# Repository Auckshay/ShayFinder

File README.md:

# ShayFinder
A Multimedia Controller

(3D model)

## Why I made this project

I've always wanted a fast way to pause and play my media without compremising the function of any keys on my main keyboard. I saw the pathfinder template as a great place to build on my desire.

## Schematic

## PCB

## B.O.M.

|Name                                |Purpose                                          |Quantity|Total Cost (USD)|Link                                                                             |Distributor|
|------------------------------------|-------------------------------------------------|--------|----------------|---------------------------------------------------------------------------------|-----------|
|PCB                                 |For mounting and connecting all components       |5       |5.00            |http://pcbway.com/orderonline.aspx?outsideid=923c8937-0e41-439f-b9aa-470abffc90b2|PCBWAY     |
|220 ohm Reistors                    |so LEDs don't burn out                           |1       |0.99            |https://www.aliexpress.us/item/3256811700129159.html                             |AliExpress |
|LEDs                                |indicator for when switch is pressed (looks cool)|1       |2.32            |https://www.aliexpress.us/item/3256807854481666.html                             |AliExpress |
|Keyboard Switches (Cherry MX Design)|Human Interaction for controlling device         |1       |3.13            |https://www.aliexpress.us/item/3256806762410255.html                             |AliExpress |
|Seeedorino XIAO RP2040              |The brains for my entire project                 |1       |10.99           |https://a.co/d/0gEoytSN                                                          |Amazon     |

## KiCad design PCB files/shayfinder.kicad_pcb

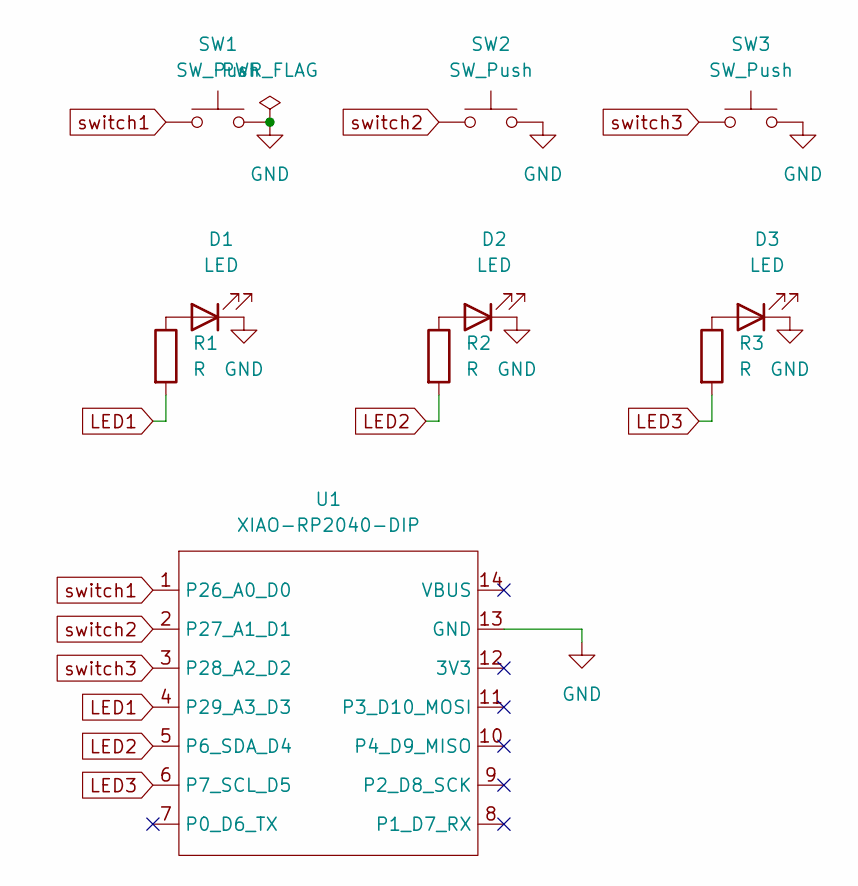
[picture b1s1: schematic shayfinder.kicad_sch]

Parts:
D1, D2, D3: LED; LED_D3.0mm_FlatTop
R1, R2, R3: R; R_Axial_DIN0204_L3.6mm_D1.6mm_P5.08mm_Horizontal
SW1, SW2, SW3: SW_Push; SW_Cherry_MX_1.00u_PCB
U1: XIAO-RP2040-DIP

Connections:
GND: D1.1 (K), D2.1 (K), D3.1 (K), SW1.2, SW2.2, SW3.2, U1.13 (GND)
LED1: R1.2, U1.4 (P29_A3_D3)
LED2: R2.2, U1.5 (P6_SDA_D4)
LED3: R3.2, U1.6 (P7_SCL_D5)
unnamed: D1.2 (A), R1.1
unnamed: D2.2 (A), R2.1
unnamed: D3.2 (A), R3.1
switch1: SW1.1, U1.1 (P26_A0_D0)
switch2: SW2.1, U1.2 (P27_A1_D1)
switch3: SW3.1, U1.3 (P28_A2_D2)

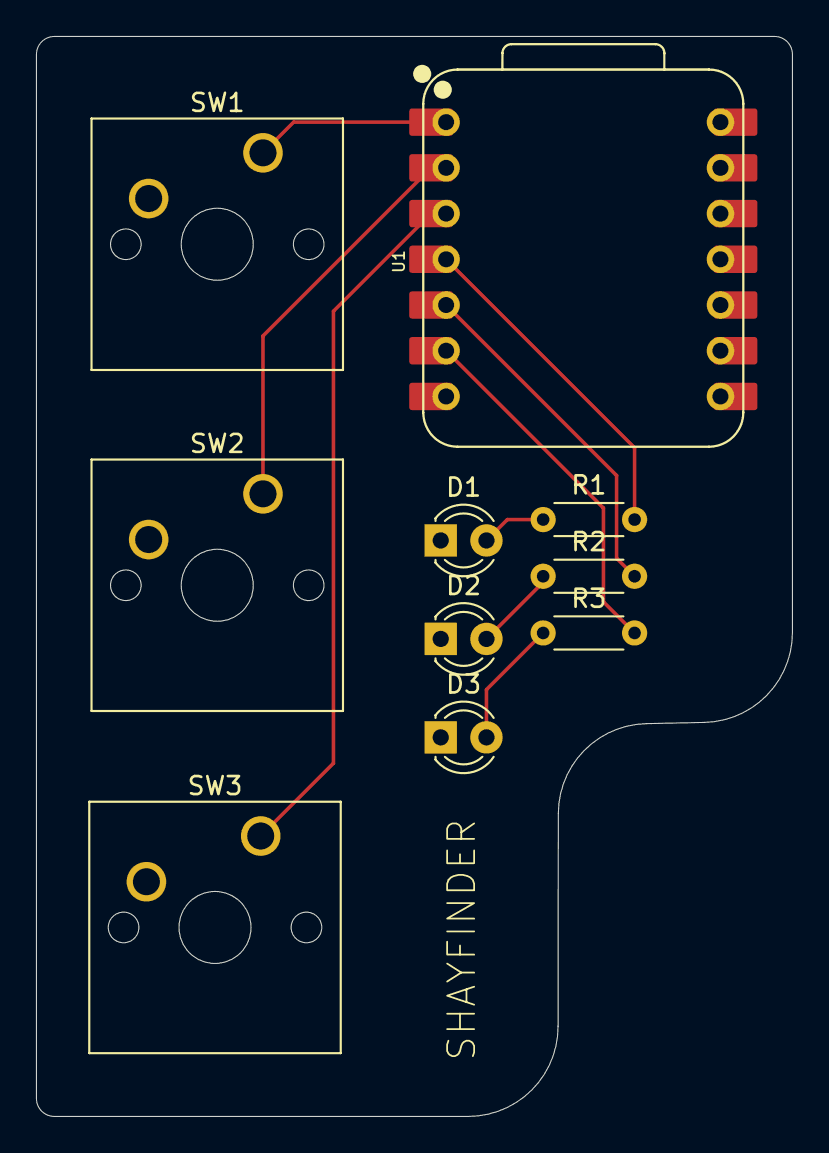
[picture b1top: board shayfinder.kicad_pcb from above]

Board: 2 copper layers, 42.0 x 60.0 mm, 10 parts (0 on the bottom side), 10 nets.

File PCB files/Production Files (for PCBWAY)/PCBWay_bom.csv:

Designator,Quantity,Value,Footprint,Package,MPN,DNP,Mount_Type,Description,KiLib_Generator,Sim.Pins
"D1, D2, D3",3,LED,LED_D3.0mm_FlatTop,,,,tht,Light emitting diode,LED/THT,1=K 2=A
"R1, R2, R3",3,R,R_Axial_DIN0204_L3.6mm_D1.6mm_P5.08mm_Horizontal,,,,tht,Resistor,resistor/THT,
"SW1, SW2, SW3",3,SW_Push,SW_Cherry_MX_1.00u_PCB,,,,tht,"Push button switch, generic, two pins",,
U1,1,XIAO-RP2040-DIP,XIAO-RP2040-DIP,,,,smt,,,

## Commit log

2026-06-18 Enhance README with project details and images
    Added detailed project information including purpose, schematic, PCB, and bill of materials.
2026-06-18 Added BOM
2026-06-18 Main 3D Model Upload
2026-06-18 PCB files + associated step files
2026-06-18 Rename Directory and Removing Reduant Files
2026-06-18 Fixed type in Readme BOM and BOM BOM
2026-06-18 Complied Firmware
2026-06-18 Source Code for Firmware
2026-06-19 Added PCB production files
2026-06-19 removed unzipped data in favor for zipped data
